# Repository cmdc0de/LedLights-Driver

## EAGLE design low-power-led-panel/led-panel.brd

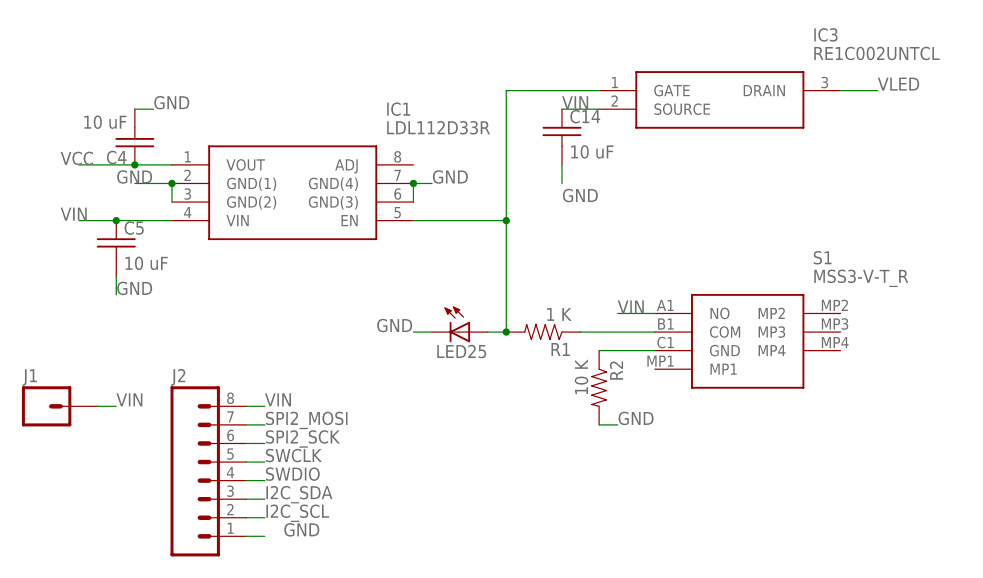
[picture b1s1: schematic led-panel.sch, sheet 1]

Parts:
C4, C5, C14: 10 uF; C0805K
IC1: LDL112D33R; SOIC127P600X175-8N
IC3: RE1C002UNTCL; SOT50P160X85-3N
J1: M01HVIA; HOME_VIA
J2: M08LONGPADS; 1X08_LONGPADS
LED25: LEDXZCFBB53W-8VF-2MA-LED; LEDC1606X95N
R1: 1 K; R0805
R2: 10 K; R0805
S1: MSS3-V-T_R; MSS3VTR

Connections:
GND: C4.2, C5.2, C14.2, IC1.2 (GND(1)), IC1.3 (GND(2)), IC1.6 (GND(3)), IC1.7 (GND(4)), J2.1, LED25.2 (C), R2.2; also elsewhere on the board
I2C_SCL: J2.2; also elsewhere on the board
I2C_SDA: J2.3; also elsewhere on the board
unnamed: R2.1, S1.C1 (GND)
unnamed: R1.1, S1.B1 (COM)
unnamed: IC1.5 (EN), IC3.1 (GATE), LED25.1 (A), R1.2
SPI2_MOSI: J2.7; also elsewhere on the board
SPI2_SCK: J2.6; also elsewhere on the board
SWCLK: J2.5; also elsewhere on the board
SWDIO: J2.4; also elsewhere on the board
VCC: C4.1, IC1.1 (VOUT); also elsewhere on the board
VIN: C5.1, C14.1, IC1.4 (VIN), IC3.2 (SOURCE), J1.1, J2.8, S1.A1 (NO)
VLED: IC3.3 (DRAIN); also elsewhere on the board

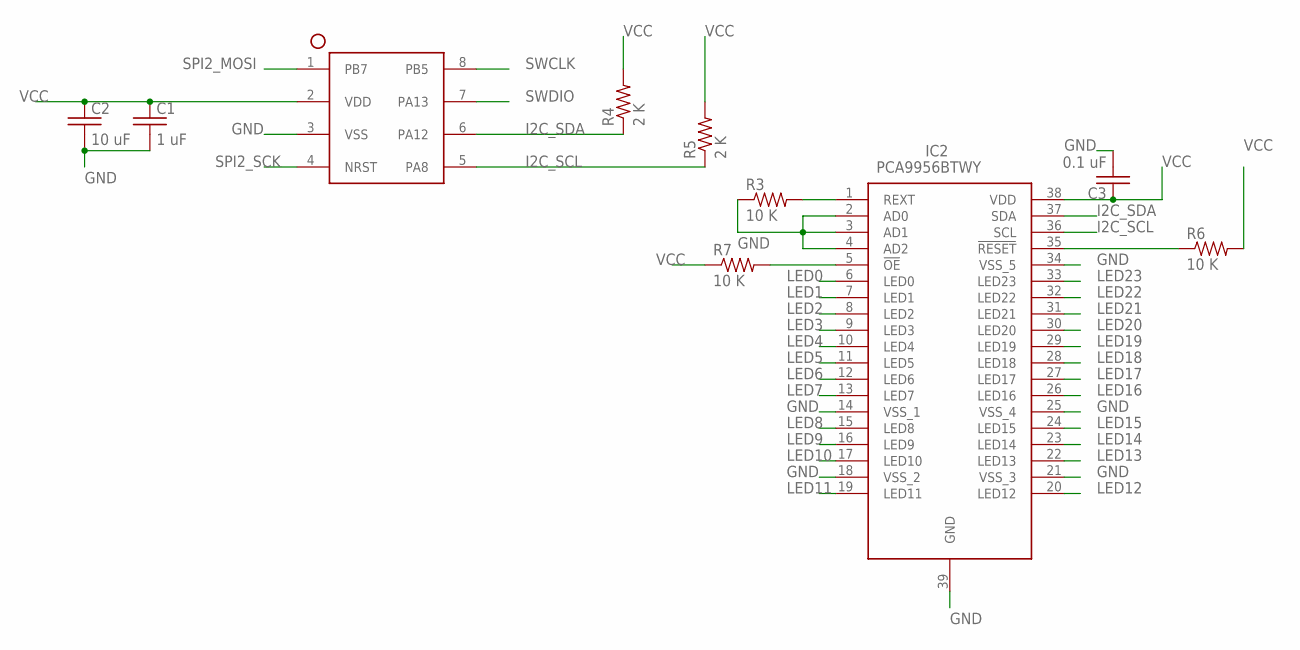
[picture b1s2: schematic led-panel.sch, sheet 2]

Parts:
C1: 1 uF; C0805K
C2: 10 uF; C0805K
C3: 0.1 uF; C0805K
IC2: PCA9956BTWY; SOP50P640X110-39N
R3, R6, R7: 10 K; 0805
R4, R5: 2 K; 0805
U$1: STM32G031S08N; SOIC127P600X175-8N

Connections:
GND: C1.2, C2.2, C3.2, IC2.2 (AD0), IC2.3 (AD1), IC2.4 (AD2), IC2.14 (VSS_1), IC2.18 (VSS_2), IC2.21 (VSS_3), IC2.25 (VSS_4), IC2.34 (VSS_5), IC2.39 (GND), R3.1, U$1.3 (VSS); also elsewhere on the board
I2C_SCL: IC2.36 (SCL), R5.1, U$1.5 (PA8); also elsewhere on the board
I2C_SDA: IC2.37 (SDA), R4.1, U$1.6 (PA12); also elsewhere on the board
LED0: IC2.6 (LED0); also elsewhere on the board
LED1: IC2.7 (LED1); also elsewhere on the board
LED2: IC2.8 (LED2); also elsewhere on the board
LED3: IC2.9 (LED3); also elsewhere on the board
LED4: IC2.10 (LED4); also elsewhere on the board
LED5: IC2.11 (LED5); also elsewhere on the board
LED6: IC2.12 (LED6); also elsewhere on the board
LED7: IC2.13 (LED7); also elsewhere on the board
LED8: IC2.15 (LED8); also elsewhere on the board
LED9: IC2.16 (LED9); also elsewhere on the board
LED10: IC2.17 (LED10); also elsewhere on the board
LED11: IC2.19 (LED11); also elsewhere on the board
LED12: IC2.20 (LED12); also elsewhere on the board
LED13: IC2.22 (LED13); also elsewhere on the board
LED14: IC2.23 (LED14); also elsewhere on the board
LED15: IC2.24 (LED15); also elsewhere on the board
LED16: IC2.26 (LED16); also elsewhere on the board
LED17: IC2.27 (LED17); also elsewhere on the board
LED18: IC2.28 (LED18); also elsewhere on the board
LED19: IC2.29 (LED19); also elsewhere on the board
LED20: IC2.30 (LED20); also elsewhere on the board
LED21: IC2.31 (LED21); also elsewhere on the board
LED22: IC2.32 (LED22); also elsewhere on the board
LED23: IC2.33 (LED23); also elsewhere on the board
unnamed: IC2.1 (REXT), R3.2
unnamed: IC2.5 (!OE), R7.2
unnamed: IC2.35 (!RESET), R6.1
SPI2_MOSI: U$1.1 (PB7); also elsewhere on the board
SPI2_SCK: U$1.4 (NRST); also elsewhere on the board
SWCLK: U$1.8 (PB5); also elsewhere on the board
SWDIO: U$1.7 (PA13); also elsewhere on the board
VCC: C1.1, C2.1, C3.1, IC2.38 (VDD), R4.2, R5.2, R6.2, R7.1, U$1.2 (VDD); also elsewhere on the board

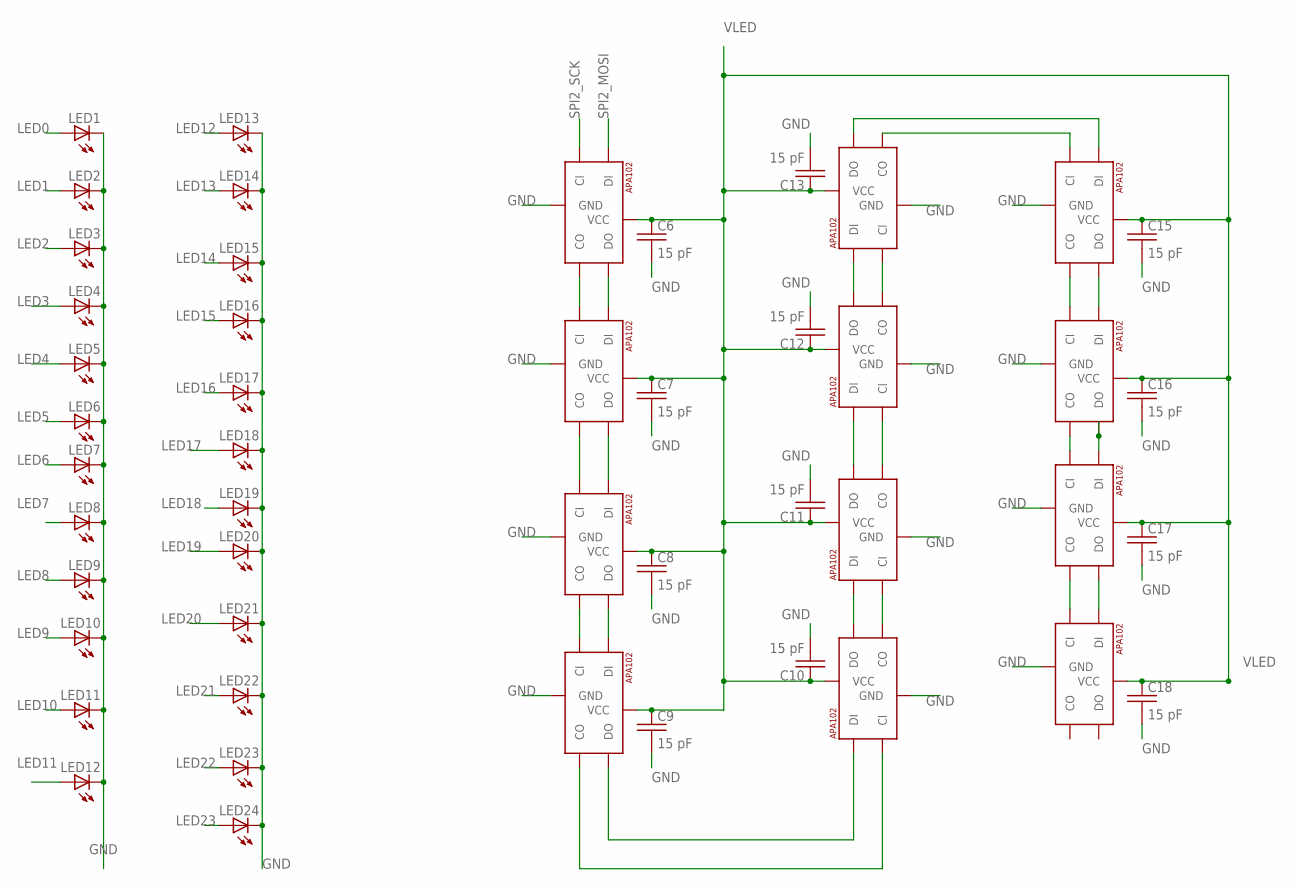
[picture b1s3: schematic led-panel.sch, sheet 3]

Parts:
C6, C7, C8, C9, C10, C11, C12, C13, C15, C16, C17, C18: 15 pF; C0805K
LED1, LED2, LED3, LED4, LED5, LED6, LED7, LED8, LED9, LED10, LED11, LED12, LED13, LED14, LED15, LED16, LED17, LED18, LED19, LED20, LED21, LED22, LED23, LED24: LEDXZCFBB53W-8VF-2MA-LED; LEDC1606X95N
U$2, U$4, U$5, U$6, U$7, U$8, U$9, U$10, U$11, U$12, U$13, U$14: APA1025050; APA102_5050

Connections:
GND: C6.2, C7.2, C8.2, C9.2, C10.2, C11.2, C12.2, C13.2, C15.2, C16.2, C17.2, C18.2, LED1.2 (C), LED2.2 (C), LED3.2 (C), LED4.2 (C), LED5.2 (C), LED6.2 (C), LED7.2 (C), LED8.2 (C), LED9.2 (C), LED10.2 (C), LED11.2 (C), LED12.2 (C), LED13.2 (C), LED14.2 (C), LED15.2 (C), LED16.2 (C), LED17.2 (C), LED18.2 (C), LED19.2 (C), LED20.2 (C), LED21.2 (C), LED22.2 (C), LED23.2 (C), LED24.2 (C), U$2.6 (GND), U$4.6 (GND), U$5.6 (GND), U$6.6 (GND), U$7.6 (GND), U$8.6 (GND), U$9.6 (GND), U$10.6 (GND), U$11.6 (GND), U$12.6 (GND), U$13.6 (GND), U$14.6 (GND); also elsewhere on the board
LED0: LED1.1 (A); also elsewhere on the board
LED1: LED2.1 (A); also elsewhere on the board
LED2: LED3.1 (A); also elsewhere on the board
LED3: LED4.1 (A); also elsewhere on the board
LED4: LED5.1 (A); also elsewhere on the board
LED5: LED6.1 (A); also elsewhere on the board
LED6: LED7.1 (A); also elsewhere on the board
LED7: LED8.1 (A); also elsewhere on the board
LED8: LED9.1 (A); also elsewhere on the board
LED9: LED10.1 (A); also elsewhere on the board
LED10: LED11.1 (A); also elsewhere on the board
LED11: LED12.1 (A); also elsewhere on the board
LED12: LED13.1 (A); also elsewhere on the board
LED13: LED14.1 (A); also elsewhere on the board
LED14: LED15.1 (A); also elsewhere on the board
LED15: LED16.1 (A); also elsewhere on the board
LED16: LED17.1 (A); also elsewhere on the board
LED17: LED18.1 (A); also elsewhere on the board
LED18: LED19.1 (A); also elsewhere on the board
LED19: LED20.1 (A); also elsewhere on the board
LED20: LED21.1 (A); also elsewhere on the board
LED21: LED22.1 (A); also elsewhere on the board
LED22: LED23.1 (A); also elsewhere on the board
LED23: LED24.1 (A); also elsewhere on the board
unnamed: U$2.2 (CO), U$4.5 (CI)
unnamed: U$2.3 (DO), U$4.4 (DI)
unnamed: U$4.2 (CO), U$5.5 (CI)
unnamed: U$4.3 (DO), U$5.4 (DI)
unnamed: U$5.3 (DO), U$6.4 (DI)
unnamed: U$5.2 (CO), U$6.5 (CI)
unnamed: U$6.3 (DO), U$7.4 (DI)
unnamed: U$6.2 (CO), U$7.5 (CI)
unnamed: U$7.3 (DO), U$8.4 (DI)
unnamed: U$7.2 (CO), U$8.5 (CI)
unnamed: U$8.3 (DO), U$9.4 (DI)
unnamed: U$8.2 (CO), U$9.5 (CI)
unnamed: U$9.2 (CO), U$10.5 (CI)
unnamed: U$9.3 (DO), U$10.4 (DI)
unnamed: U$11.3 (DO), U$12.4 (DI)
unnamed: U$11.2 (CO), U$12.5 (CI)
unnamed: U$13.3 (DO), U$14.4 (DI)
unnamed: U$13.2 (CO), U$14.5 (CI)
unnamed: U$12.2 (CO), U$13.5 (CI)
unnamed: U$12.3 (DO), U$13.4 (DI)
unnamed: U$10.2 (CO), U$11.5 (CI)
unnamed: U$10.3 (DO), U$11.4 (DI)
SPI2_MOSI: U$2.4 (DI); also elsewhere on the board
SPI2_SCK: U$2.5 (CI); also elsewhere on the board
VLED: C6.1, C7.1, C8.1, C9.1, C10.1, C11.1, C12.1, C13.1, C15.1, C16.1, C17.1, C18.1, U$2.1 (VCC), U$4.1 (VCC), U$5.1 (VCC), U$6.1 (VCC), U$7.1 (VCC), U$8.1 (VCC), U$9.1 (VCC), U$10.1 (VCC), U$11.1 (VCC), U$12.1 (VCC), U$13.1 (VCC), U$14.1 (VCC); also elsewhere on the board

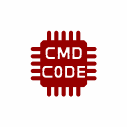
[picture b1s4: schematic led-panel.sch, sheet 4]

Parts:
U$3: CMD_C0DE_LOGOCMD_CODE_LOGO_TOP_COPPER; CMD_C0DE_LOGO_TOP_COPPER

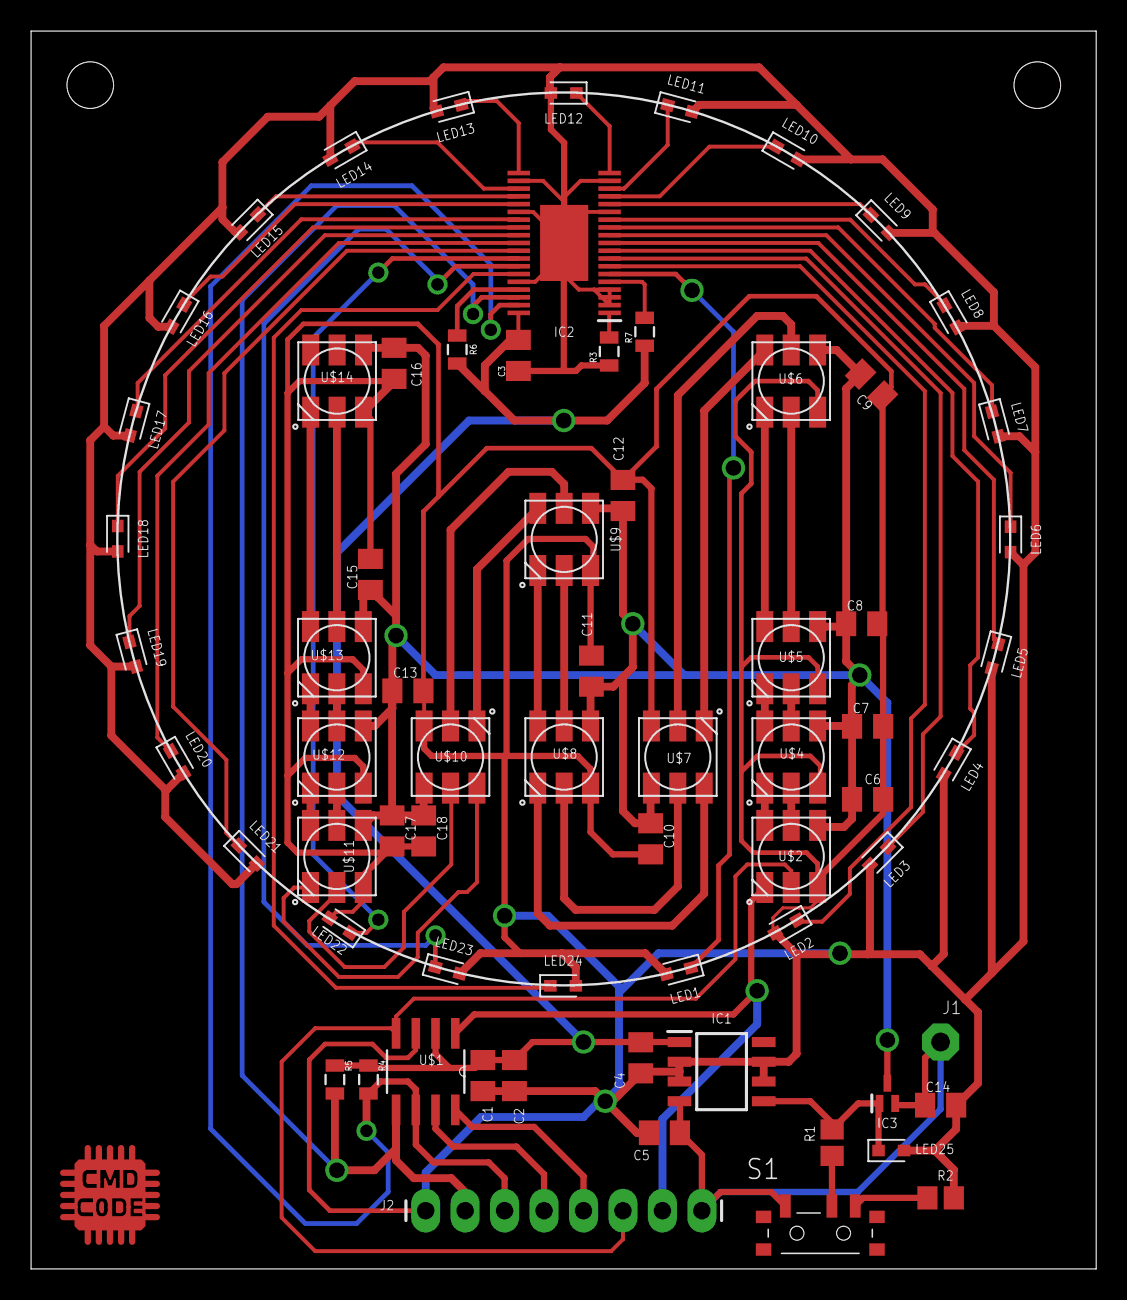
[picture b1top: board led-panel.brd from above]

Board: 2 copper layers, 68.6 x 79.7 mm, 70 parts (0 on the bottom side), 62 nets.

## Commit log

2020-03-23 LedRiver test
2020-04-09 clean up
2020-04-10 works on discovery
2020-11-13 adding docs
2020-11-13 updated to latest firmware
2020-11-13 led's pulse
